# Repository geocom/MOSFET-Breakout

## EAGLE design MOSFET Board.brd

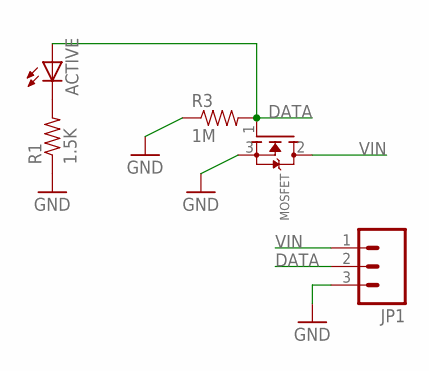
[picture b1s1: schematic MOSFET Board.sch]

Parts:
ACTIVE: LED0603; LED-0603
JP1: M03POLAR; MOLEX-1X3
MOSFET: MOSFET-NGDS_TO220V; TO220V
R1: 1.5K; 1206
R3: 1M; 1206

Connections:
DATA: ACTIVE.A, JP1.2, MOSFET.1 (G), R3.2
GND: JP1.3, MOSFET.3 (S), R1.1, R3.1
unnamed: ACTIVE.C, R1.2
VIN: JP1.1, MOSFET.2 (D)

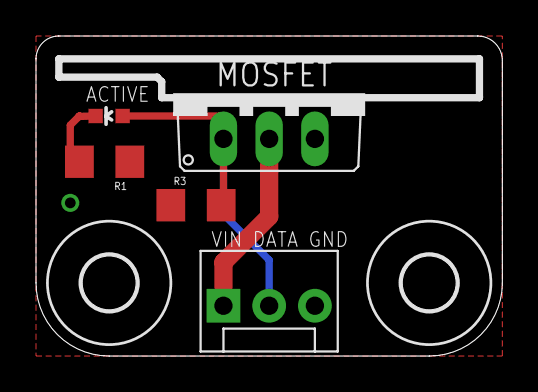
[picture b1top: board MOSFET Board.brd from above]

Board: 2 copper layers, 25.9 x 17.8 mm, 8 parts (1 on the bottom side), 4 nets.

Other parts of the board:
U$1, U$2: 3,0
U$3: OSHW-LOGO-S

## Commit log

2014-04-19 Inital Commit

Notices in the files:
parts and their libraries:
SparkFun-Passives: Licensing: CC v3.0 Share-Alike You are welcome to use this library for commercial purposes.
